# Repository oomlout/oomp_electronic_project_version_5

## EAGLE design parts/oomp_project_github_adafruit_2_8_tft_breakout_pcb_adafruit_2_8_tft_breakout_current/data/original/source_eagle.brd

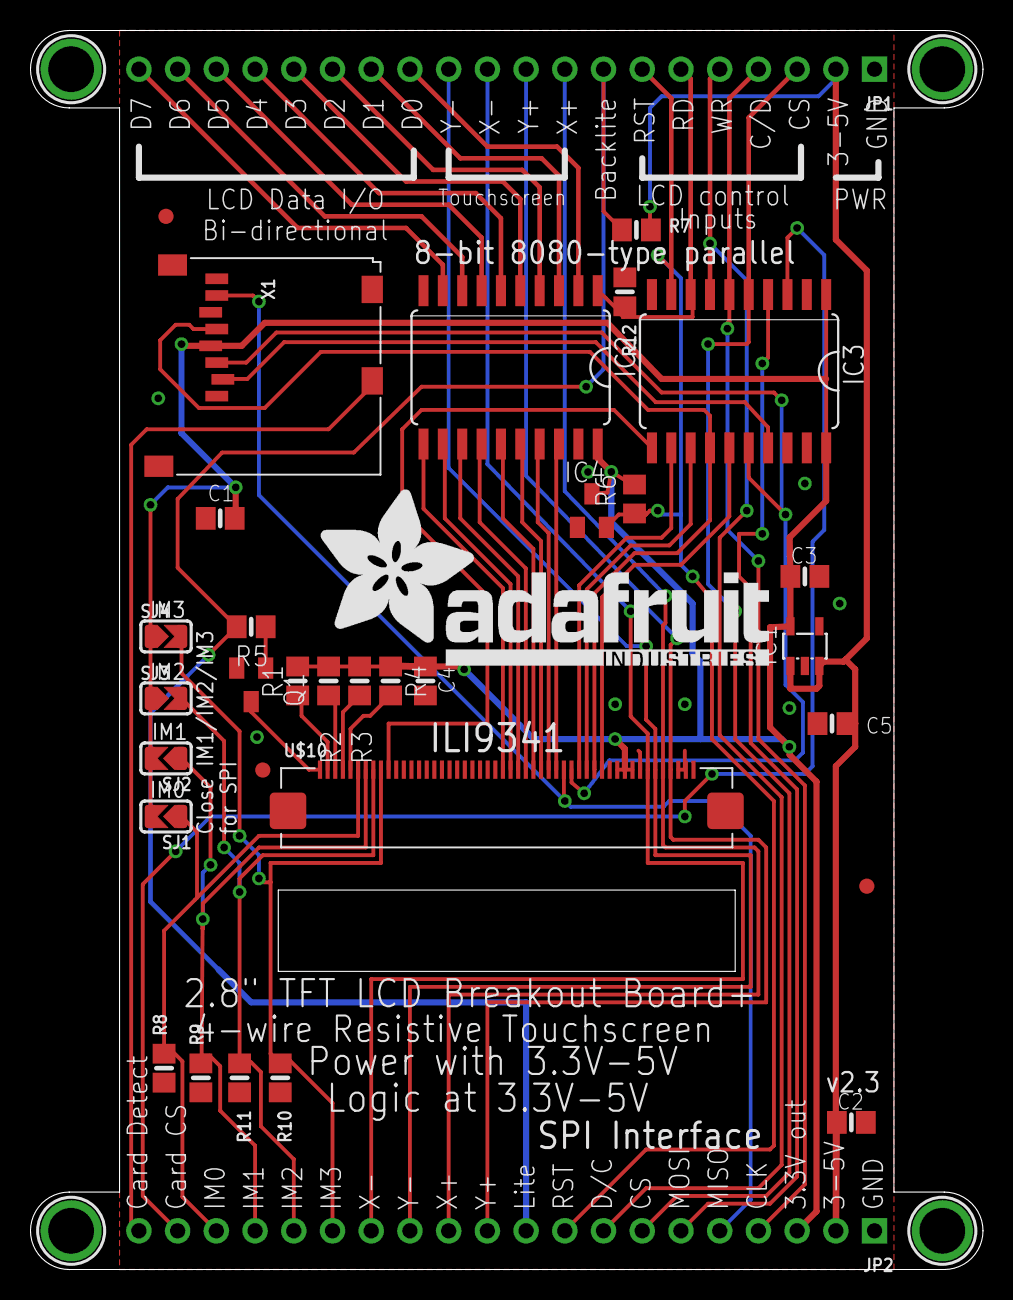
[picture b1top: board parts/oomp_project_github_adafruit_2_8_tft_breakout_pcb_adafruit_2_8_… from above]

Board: 2 copper layers, 62.5 x 81.3 mm, 38 parts (1 on the bottom side), 50 nets.

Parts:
C1, C4: 0.1uF; 0805-NO
C2, C3, C5: 10uF; 0805-NO
IC1: MIC5225-3.3; SOT23-5L
IC2, IC3: 74LVC245; SO20W
IC4: APX803-SAG; SOT23
JP1, JP2: 1X20_ROUND
Q1: MMBT2222; SOT23-BEC
R1, R2, R3, R4: 10; 0805-NO
R5, R7: 1K; 0805-NO
R6: 10K; R0805
R8, R9, R10, R11, R12: 10K; 0805-NO
SJ1, SJ2, SJ3, SJ4: SOLDERJUMPER_ARROW_NOPASTE
U$7, U$15, U$16, U$17: MOUNTINGHOLE3.0THIN; MOUNTINGHOLE_3.0_PLATEDTHIN
U$9, U$11, U$23: FIDUCIAL; FIDUCIAL_1MM
U$10: DISP_LCD_1.28IN_240X320_50PIN; TFT_2.83IN_240X320_50PIN
U$19: ADAFRUIT_TEXT_30MM
X1: MICROSD

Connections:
+5V: C2.1, C5.1, IC1.1, IC1.3, JP1.2, JP2.2, R7.2
CARDDET: JP2.20, X1.CD2
GND: C1.2, C2.2, C3.2, C4.2, C5.2, IC1.2, IC2.10, IC2.19, IC3.10, IC3.19, IC4.1, JP1.1, JP2.1, Q1.E, R8.1, R9.1, R10.2, R11.2, R12.1, U$10.43, U$10.48, U$10.49, U$10.50, X1.6, X1.MT1, X1.MT2
IM0: JP2.18, R8.2, SJ1.1, U$10.6
IM1: JP2.17, R9.2, SJ2.1, U$10.7
IM2: JP2.16, R11.1, SJ3.2, U$10.8
IM3: JP2.15, R10.1, SJ4.2, U$10.9
LCD_CS: IC3.15, U$10.38
LCD_CS_5V: IC3.5, JP1.3, JP2.7
LCD_DATA0: IC2.18, U$10.32
LCD_DATA0_5V: IC2.2, JP1.13
LCD_DATA1: IC2.17, U$10.31
LCD_DATA1_5V: IC2.3, JP1.14
LCD_DATA2: IC2.16, U$10.30
LCD_DATA2_5V: IC2.4, JP1.15
LCD_DATA3: IC2.15, U$10.29
LCD_DATA3_5V: IC2.5, JP1.16
LCD_DATA4: IC2.14, U$10.28
LCD_DATA4_5V: IC2.6, JP1.17
LCD_DATA5: IC2.13, U$10.27
LCD_DATA5_5V: IC2.7, JP1.18
LCD_DATA6: IC2.12, U$10.26
LCD_DATA6_5V: IC2.8, JP1.19
LCD_DATA7: IC2.11, U$10.25
LCD_DATA7_5V: IC2.9, JP1.20
LCD_LITE: JP1.8, JP2.10, R5.1, R7.1
LCD_RD: IC3.12, U$10.35
LCD_RD_5V: IC2.1, IC3.8, JP1.6, R12.2
LCD_RS: IC3.14, U$10.37, X1.5
LCD_RST: IC3.11, U$10.10
LCD_RST_5V: IC3.9, IC4.2, JP1.7, JP2.9, R6.1
LCD_RS_5V: IC3.6, JP1.4, JP2.4
LCD_WR: IC3.13, U$10.36
LCD_WR_5V: IC3.7, JP1.5, JP2.8
LCD_X+: JP1.9, JP2.12, U$10.46
LCD_X-: JP1.11, JP2.14, U$10.44
LCD_Y+: JP1.10, JP2.11, U$10.47
LCD_Y-: JP1.12, JP2.13, U$10.45
unnamed: R4.2, U$10.5
unnamed: R1.2, U$10.2
unnamed: R2.2, U$10.3
unnamed: R3.2, U$10.4
unnamed: Q1.C, U$10.1
unnamed: Q1.B, R5.2
SDI_3V: IC3.16, U$10.34, X1.3
SDI_5V: IC3.4, JP2.6
SDO: JP2.5, U$10.33, X1.7
SD_CS_3V: IC3.17, X1.2
SD_CS_5V: IC3.3, JP2.19
VCC: C1.1, C3.1, C4.1, IC1.5, IC2.20, IC3.1, IC3.20, IC4.3, JP2.3, R1.1, R2.1, R3.1, R4.1, R6.2, SJ1.2, SJ2.2, SJ3.1, SJ4.1, U$10.40, U$10.41, U$10.42, X1.4

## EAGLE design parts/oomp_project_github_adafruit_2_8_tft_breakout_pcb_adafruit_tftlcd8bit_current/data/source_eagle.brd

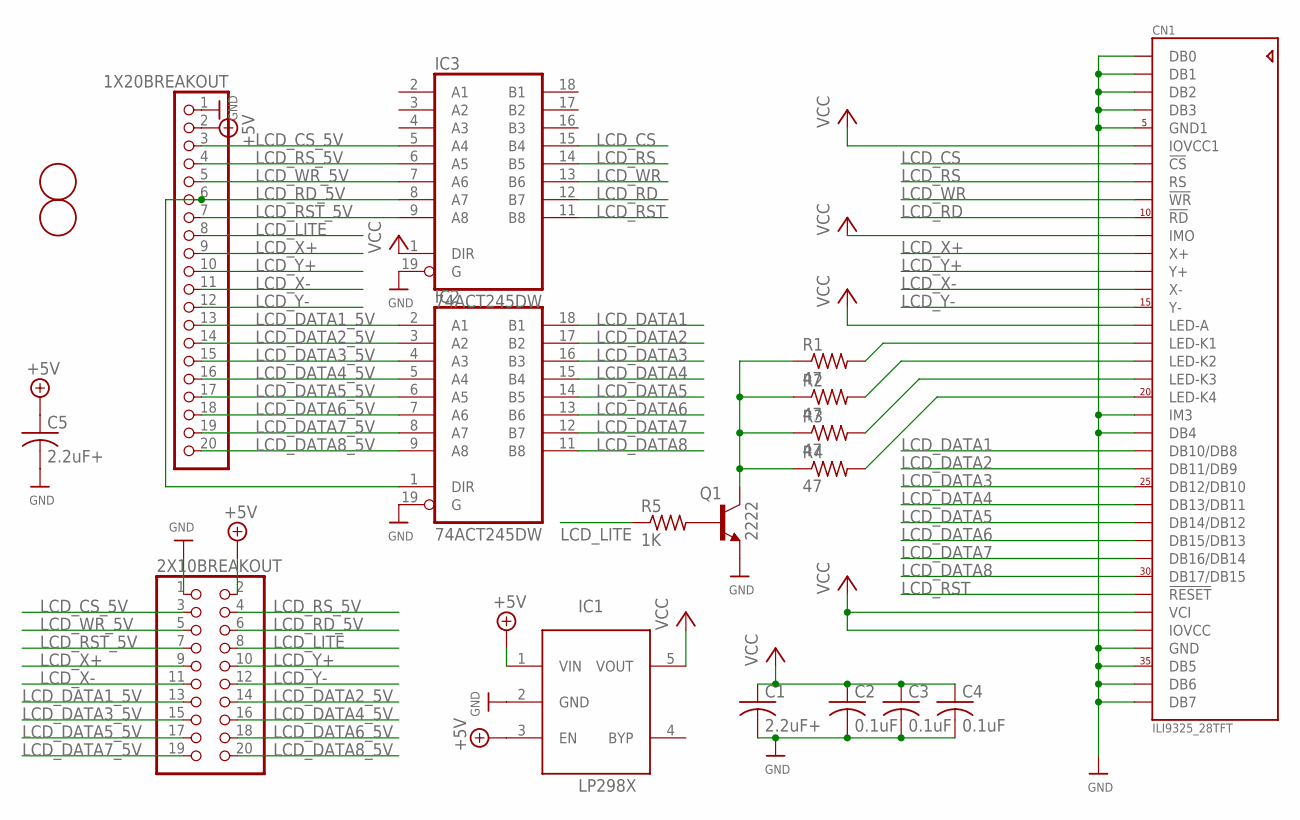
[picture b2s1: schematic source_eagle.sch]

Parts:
1X20BREAKOUT: PINHD-1X20; 1X20
2X10BREAKOUT: PINHD-2X10; 2X10
C1, C5: 2.2uF+; C0805K
C2, C3, C4: 0.1uF; C0805K
CN1: ILI9325_28TFT; ILI9325_28INCH_TS
IC1: LP298XS; SOT23-5L
IC2, IC3: 74ACT245DW; SO20W
Q1: 2222; SOT23-BEC
R1, R2, R3, R4: 47; R0805
R5: 1K; R0805
U$9, U$11: FIDUCIAL; FIDUCIAL_1MM

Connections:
+5V: 1X20BREAKOUT.2, 2X10BREAKOUT.2, C5.1, IC1.1 (VIN), IC1.3 (EN)
GND: 1X20BREAKOUT.1, 2X10BREAKOUT.1, C1.2, C2.2, C3.2, C4.2, C5.2, CN1.1 (DB0), CN1.2 (DB1), CN1.3 (DB2), CN1.4 (DB3), CN1.5 (GND1), CN1.21 (IM3), CN1.22 (DB4), CN1.34 (GND), CN1.35 (DB5), CN1.36 (DB6), CN1.37 (DB7), IC1.2 (GND), IC2.10 (GND), IC2.19 (G), IC3.10 (GND), IC3.19 (G), Q1.E
LCD_CS: CN1.7 (!CS), IC3.15 (B4)
LCD_CS_5V: 1X20BREAKOUT.3, 2X10BREAKOUT.3, IC3.5 (A4)
LCD_DATA1: CN1.23 (DB10/DB8), IC2.18 (B1)
LCD_DATA1_5V: 1X20BREAKOUT.13, 2X10BREAKOUT.13, IC2.2 (A1)
LCD_DATA2: CN1.24 (DB11/DB9), IC2.17 (B2)
LCD_DATA2_5V: 1X20BREAKOUT.14, 2X10BREAKOUT.14, IC2.3 (A2)
LCD_DATA3: CN1.25 (DB12/DB10), IC2.16 (B3)
LCD_DATA3_5V: 1X20BREAKOUT.15, 2X10BREAKOUT.15, IC2.4 (A3)
LCD_DATA4: CN1.26 (DB13/DB11), IC2.15 (B4)
LCD_DATA4_5V: 1X20BREAKOUT.16, 2X10BREAKOUT.16, IC2.5 (A4)
LCD_DATA5: CN1.27 (DB14/DB12), IC2.14 (B5)
LCD_DATA5_5V: 1X20BREAKOUT.17, 2X10BREAKOUT.17, IC2.6 (A5)
LCD_DATA6: CN1.28 (DB15/DB13), IC2.13 (B6)
LCD_DATA6_5V: 1X20BREAKOUT.18, 2X10BREAKOUT.18, IC2.7 (A6)
LCD_DATA7: CN1.29 (DB16/DB14), IC2.12 (B7)
LCD_DATA7_5V: 1X20BREAKOUT.19, 2X10BREAKOUT.19, IC2.8 (A7)
LCD_DATA8: CN1.30 (DB17/DB15), IC2.11 (B8)
LCD_DATA8_5V: 1X20BREAKOUT.20, 2X10BREAKOUT.20, IC2.9 (A8)
LCD_LITE: 1X20BREAKOUT.8, 2X10BREAKOUT.8, R5.1
LCD_RD: CN1.10 (!RD), IC3.12 (B7)
LCD_RD_5V: 1X20BREAKOUT.6, 2X10BREAKOUT.6, IC2.1 (DIR), IC3.8 (A7)
LCD_RS: CN1.8 (RS), IC3.14 (B5)
LCD_RST: CN1.31 (!RESET), IC3.11 (B8)
LCD_RST_5V: 1X20BREAKOUT.7, 2X10BREAKOUT.7, IC3.9 (A8)
LCD_RS_5V: 1X20BREAKOUT.4, 2X10BREAKOUT.4, IC3.6 (A5)
LCD_WR: CN1.9 (!WR), IC3.13 (B6)
LCD_WR_5V: 1X20BREAKOUT.5, 2X10BREAKOUT.5, IC3.7 (A6)
LCD_X+: 1X20BREAKOUT.9, 2X10BREAKOUT.9, CN1.12 (X+)
LCD_X-: 1X20BREAKOUT.11, 2X10BREAKOUT.11, CN1.14 (X-)
LCD_Y+: 1X20BREAKOUT.10, 2X10BREAKOUT.10, CN1.13 (Y+)
LCD_Y-: 1X20BREAKOUT.12, 2X10BREAKOUT.12, CN1.15 (Y-)
unnamed: CN1.20 (LED-K4), R4.2
unnamed: CN1.17 (LED-K1), R1.2
unnamed: CN1.18 (LED-K2), R2.2
unnamed: CN1.19 (LED-K3), R3.2
unnamed: Q1.C, R1.1, R2.1, R3.1, R4.1
unnamed: Q1.B, R5.2
VCC: C1.1, C2.1, C3.1, C4.1, CN1.6 (IOVCC1), CN1.11 (IMO), CN1.16 (LED-A), CN1.32 (VCI), CN1.33 (IOVCC), IC1.5 (VOUT), IC2.20 (VCC), IC3.1 (DIR), IC3.20 (VCC)

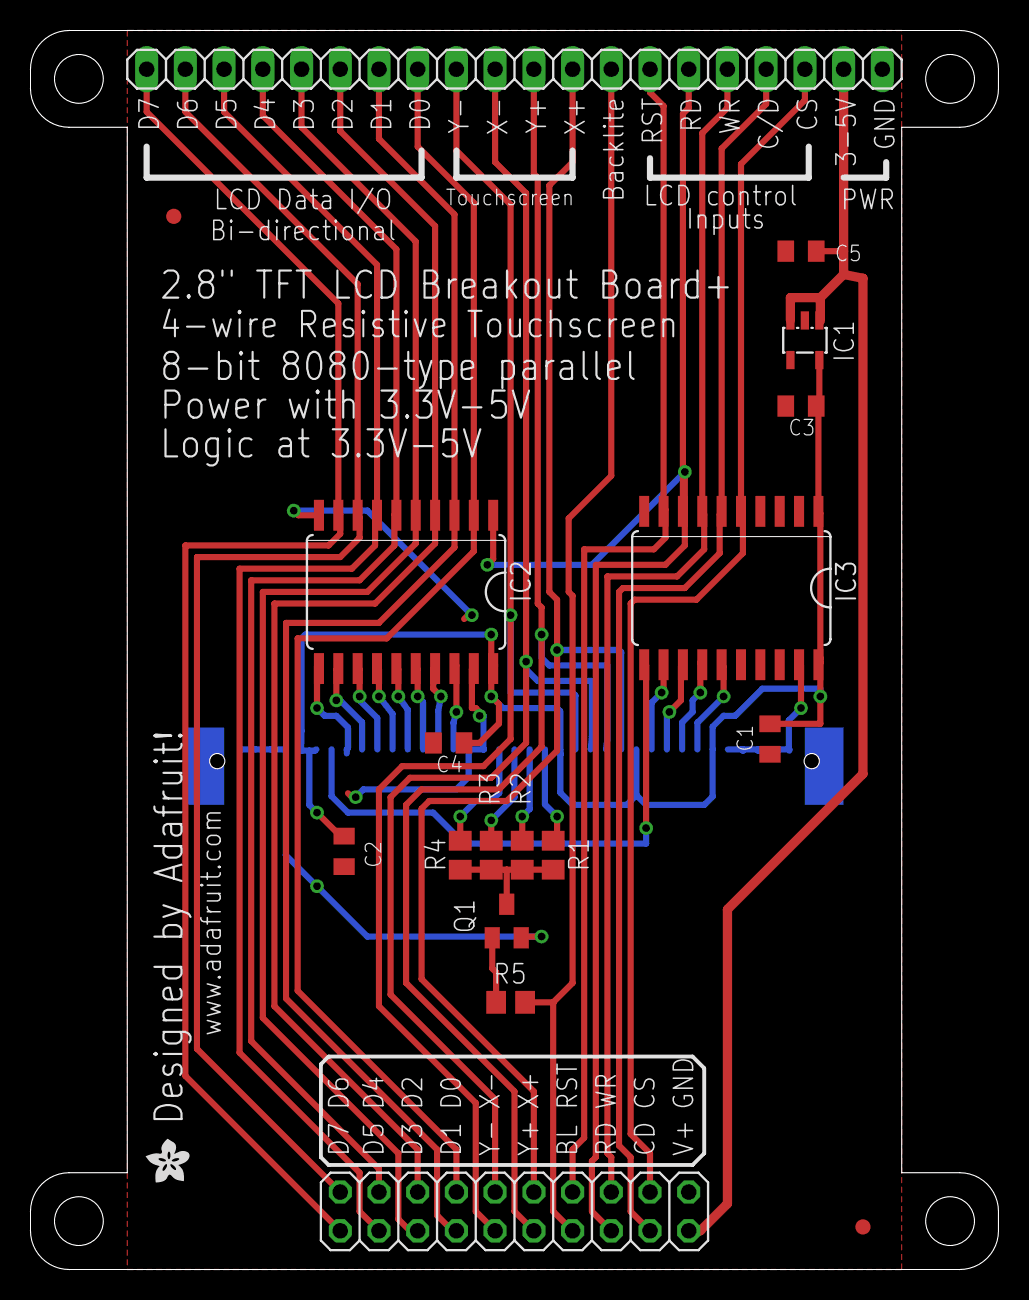
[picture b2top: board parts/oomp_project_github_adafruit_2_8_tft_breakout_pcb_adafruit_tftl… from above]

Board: 2 copper layers, 63.5 x 81.3 mm, 20 parts (1 on the bottom side), 40 nets.

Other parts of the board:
U$3: ADAFRUIT200MIL

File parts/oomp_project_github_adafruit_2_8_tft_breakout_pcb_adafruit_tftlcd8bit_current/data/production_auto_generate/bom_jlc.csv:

Comment,Designator,Footprint,LCSC Part #
,UNK1X20BREAKOUT0,Adafruit_tftlcd8bit-import-fps:1X20,C50981
,UNK2X10BREAKOUT0,Adafruit_tftlcd8bit-import-fps:2X10,
,U$3,Adafruit_tftlcd8bit-import-fps:ADAFRUIT200MIL,
0.1uF,"C2,C3,C4",Adafruit_tftlcd8bit-import-fps:C0805K,
1K,R5,Adafruit_tftlcd8bit-import-fps:R0805,C17513
2.2uF+,"C1,C5",Adafruit_tftlcd8bit-import-fps:C0805K,
2222,Q1,Adafruit_tftlcd8bit-import-fps:SOT23-BEC,
47,"R1,R2,R3,R4",Adafruit_tftlcd8bit-import-fps:R0805,C2907268
74ACT245DW,"IC2,IC3",Adafruit_tftlcd8bit-import-fps:SO20W,
FIDUCIAL,"U$9,U$11",Adafruit_tftlcd8bit-import-fps:FIDUCIAL_1MM,
ILI9325_28TFT,CN1,Adafruit_tftlcd8bit-import-fps:ILI9325_28INCH_TS,
LP298XS,IC1,Adafruit_tftlcd8bit-import-fps:SOT23-5L,

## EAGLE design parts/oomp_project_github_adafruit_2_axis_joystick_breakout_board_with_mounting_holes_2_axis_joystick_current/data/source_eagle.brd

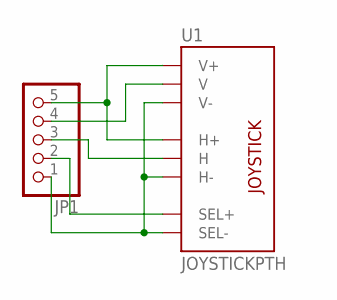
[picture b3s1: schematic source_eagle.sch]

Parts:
JP1: PINHD-1X5; 1X05
U1: JOYSTICKPTH; JOYSTICK

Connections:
unnamed: JP1.5, U1.H1 (H+), U1.V1 (V+)
unnamed: JP1.1, U1.B2A (SEL-), U1.H3 (H-), U1.V3 (V-)
unnamed: JP1.4, U1.V2 (V)
unnamed: JP1.3, U1.H2 (H)
unnamed: JP1.2, U1.B1A (SEL+)

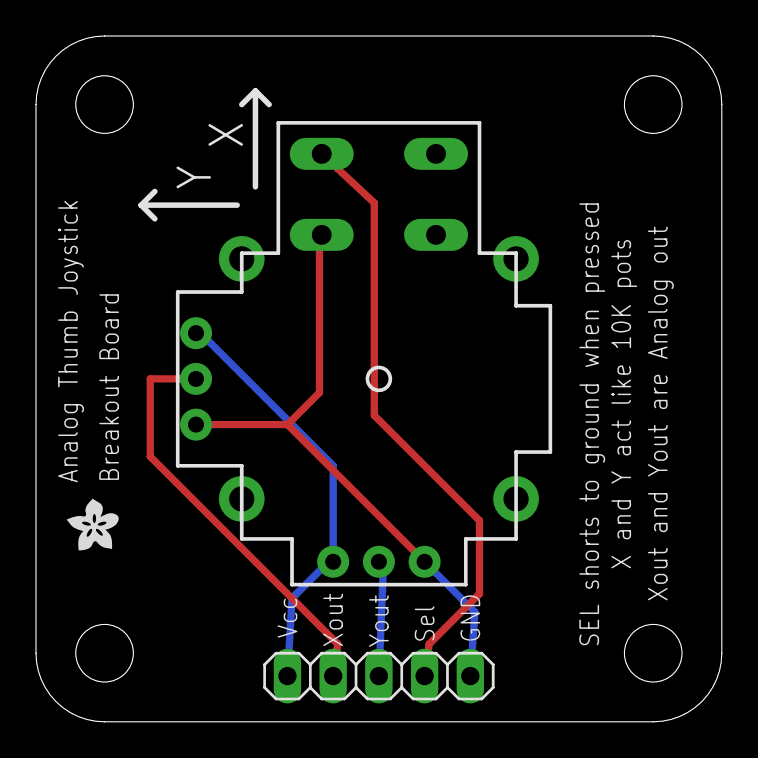
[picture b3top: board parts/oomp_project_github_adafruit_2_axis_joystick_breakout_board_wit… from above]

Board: 2 copper layers, 38.1 x 38.1 mm, 3 parts (0 on the bottom side), 5 nets.

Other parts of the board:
U$1: ADAFRUIT200MIL

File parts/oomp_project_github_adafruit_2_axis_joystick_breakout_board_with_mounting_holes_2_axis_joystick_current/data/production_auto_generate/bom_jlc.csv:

Comment,Designator,Footprint,LCSC Part #
,JP1,joystick-import-fps:1X05,C42431835
,U$1,joystick-import-fps:ADAFRUIT200MIL,
JOYSTICKPTH,U1,joystick-import-fps:JOYSTICK,

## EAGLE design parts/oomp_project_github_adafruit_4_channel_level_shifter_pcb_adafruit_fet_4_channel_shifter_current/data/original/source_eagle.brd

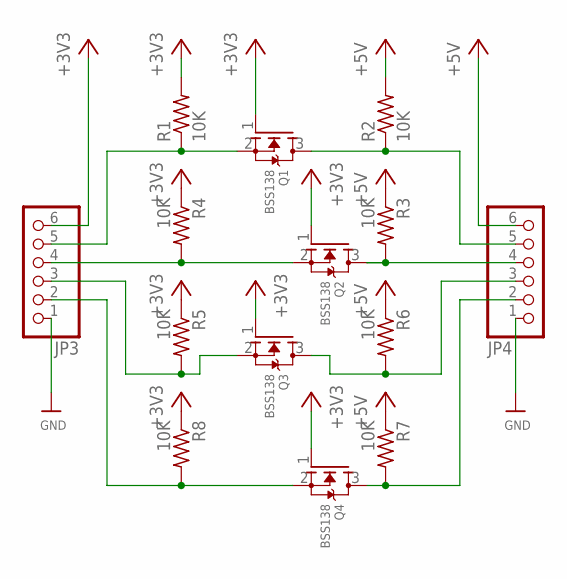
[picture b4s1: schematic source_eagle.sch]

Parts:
JP3, JP4: PINHD-1X6CB; 1X06-CLEANBIG
Q1, Q2, Q3, Q4: BSS138; SOT23
R1, R2, R3, R4, R5, R6, R7, R8: 10K; R0805

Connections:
+3V3: JP3.6, Q1.1 (G), Q2.1 (G), Q3.1 (G), Q4.1 (G), R1.2, R4.1, R5.1, R8.1
+5V: JP4.6, R2.2, R3.1, R6.1, R7.1
GND: JP3.1, JP4.1
unnamed: JP4.3, Q3.3 (D), R6.2
unnamed: JP4.5, Q1.3 (D), R2.1
unnamed: JP3.3, Q3.2 (S), R5.2
unnamed: JP3.2, Q4.2 (S), R8.2
unnamed: JP4.2, Q4.3 (D), R7.2
unnamed: JP3.4, Q2.2 (S), R4.2
unnamed: JP4.4, Q2.3 (D), R3.2
unnamed: JP3.5, Q1.2 (S), R1.1

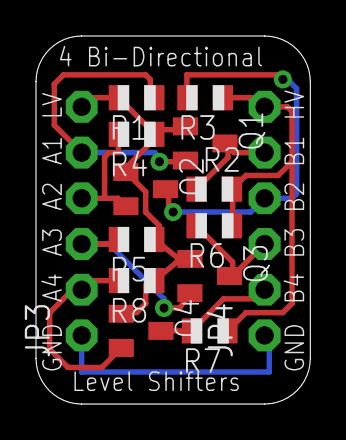
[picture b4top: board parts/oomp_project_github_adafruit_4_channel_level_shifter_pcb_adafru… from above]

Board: 2 copper layers, 15.2 x 20.4 mm, 15 parts (1 on the bottom side), 11 nets.

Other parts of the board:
U$1: ADAFRUIT_3.5MM

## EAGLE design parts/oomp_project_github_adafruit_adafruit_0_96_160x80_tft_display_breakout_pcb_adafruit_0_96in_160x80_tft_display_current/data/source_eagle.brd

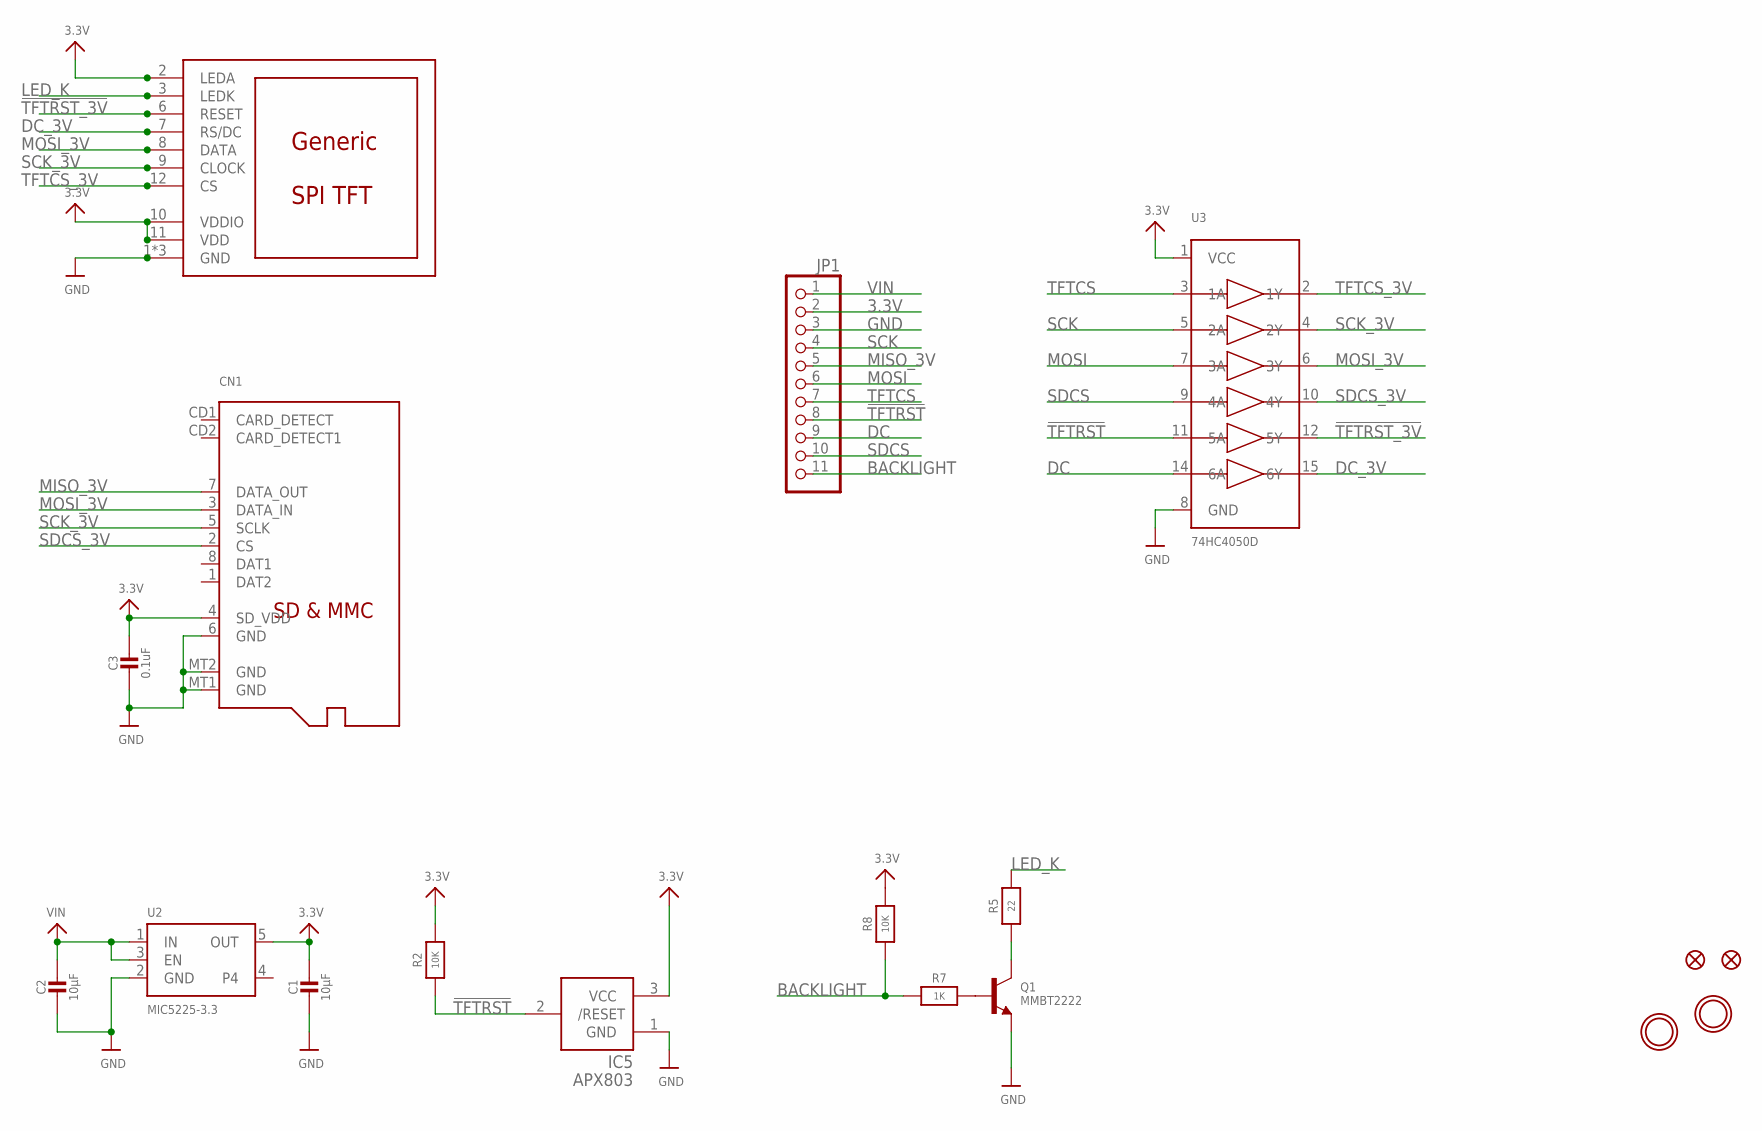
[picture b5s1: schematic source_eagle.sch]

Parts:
C1, C2: 10µF; 0805-NO
C3: 0.1uF; 0805-NO
CN1: MICROSD
FID1, FID2: FIDUCIAL_1MM
IC5: APX803; SOT23
JP1: HEADER-1X11; 1X11_ROUND
Q1: MMBT2222; SOT23-WIDE
R2, R8: 10K; 0603-NO
R5: 22; 0603-NO
R7: 1K; 0603-NO
U2: MIC5225-3.3; SOT23-5
U3: 74HC4050D; SOIC16
U$2: DISP_LCD_0.9IN_160X80; TFT_0.96IN_160X80
U$9, U$10: MOUNTINGHOLE2.5; MOUNTINGHOLE_2.5_PLATED

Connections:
3.3V: C1.1, C3.1, CN1.4 (SD_VDD), IC5.3 (VCC), JP1.2, R2.2, R8.2, U2.5 (OUT), U3.1 (VCC), U$2.2 (LEDA), U$2.10 (VDDIO), U$2.11 (VDD)
!TFTRST: IC5.2 (/RESET), JP1.8, R2.1, U3.11 (5A)
!TFTRST_3V: U3.12 (5Y), U$2.6 (RESET)
BACKLIGHT: JP1.11, R7.1, R8.1
DC: JP1.9, U3.14 (6A)
DC_3V: U3.15 (6Y), U$2.7 (RS/DC)
GND: C1.2, C2.2, C3.2, CN1.6 (GND), CN1.MT1 (GND), CN1.MT2 (GND), IC5.1 (GND), JP1.3, Q1.2 (E), U2.2 (GND), U3.8 (GND), U$2.1 (GND), U$2.5 (GND), U$2.13 (GND)
LED_K: R5.2, U$2.3 (LEDK)
MISO_3V: CN1.7 (DATA_OUT), JP1.5
MOSI: JP1.6, U3.7 (3A)
MOSI_3V: CN1.3 (DATA_IN), U3.6 (3Y), U$2.8 (DATA)
unnamed: Q1.1 (B), R7.2
unnamed: Q1.3 (C), R5.1
SCK: JP1.4, U3.5 (2A)
SCK_3V: CN1.5 (SCLK), U3.4 (2Y), U$2.9 (CLOCK)
SDCS: JP1.10, U3.9 (4A)
SDCS_3V: CN1.2 (CS), U3.10 (4Y)
TFTCS: JP1.7, U3.3 (1A)
TFTCS_3V: U3.2 (1Y), U$2.12 (CS)
VIN: C2.1, JP1.1, U2.1 (IN), U2.3 (EN)

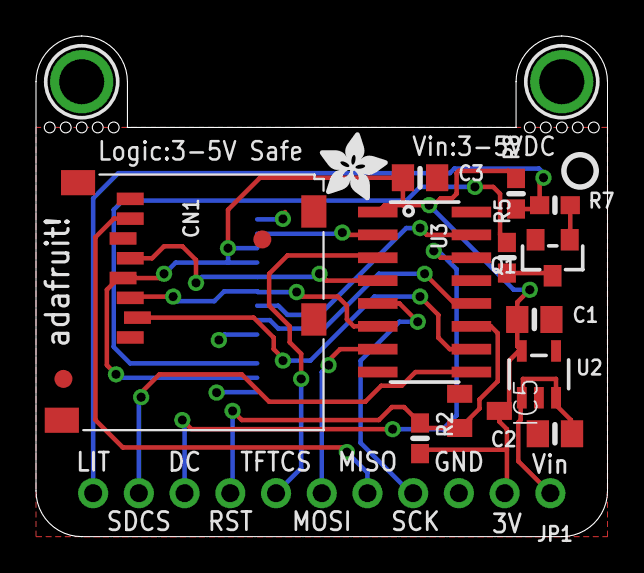
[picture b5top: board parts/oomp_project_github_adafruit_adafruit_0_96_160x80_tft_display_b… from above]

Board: 2 copper layers, 31.8 x 27.8 mm, 20 parts (1 on the bottom side), 20 nets.

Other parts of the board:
U$4: MICROSD; ADAFRUIT_3.5MM
U$6: PCBFEAT-REV-040

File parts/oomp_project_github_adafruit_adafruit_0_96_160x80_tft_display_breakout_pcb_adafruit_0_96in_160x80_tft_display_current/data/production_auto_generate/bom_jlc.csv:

Comment,Designator,Footprint,LCSC Part #
,JP1,Adafruit 0.96in 160x80 TFT Display-import-fps:1X11_ROUND,C2894934
,CN1,Adafruit 0.96in 160x80 TFT Display-import-fps:MICROSD,
,U$6,Adafruit 0.96in 160x80 TFT Display-import-fps:PCBFEAT-REV-040,
0.1uF,C3,Adafruit 0.96in 160x80 TFT Display-import-fps:0805-NO,
10K,"R2,R8",Adafruit 0.96in 160x80 TFT Display-import-fps:0603-NO,C98220
10µF,"C1,C2",Adafruit 0.96in 160x80 TFT Display-import-fps:0805-NO,
1K,R7,Adafruit 0.96in 160x80 TFT Display-import-fps:0603-NO,C2907002
22,R5,Adafruit 0.96in 160x80 TFT Display-import-fps:0603-NO,C23345
74HC4050D,U3,Adafruit 0.96in 160x80 TFT Display-import-fps:SOIC16,
APX803,IC5,Adafruit 0.96in 160x80 TFT Display-import-fps:SOT23,
DISP_LCD_0.9IN_160X80,U$2,Adafruit 0.96in 160x80 TFT Display-import-fps:TFT_0.96IN_160X80,
MIC5225-3.3,U2,Adafruit 0.96in 160x80 TFT Display-import-fps:SOT23-5,
MICROSD,U$4,Adafruit 0.96in 160x80 TFT Display-import-fps:ADAFRUIT_3.5MM,
MMBT2222,Q1,Adafruit 0.96in 160x80 TFT Display-import-fps:SOT23-WIDE,

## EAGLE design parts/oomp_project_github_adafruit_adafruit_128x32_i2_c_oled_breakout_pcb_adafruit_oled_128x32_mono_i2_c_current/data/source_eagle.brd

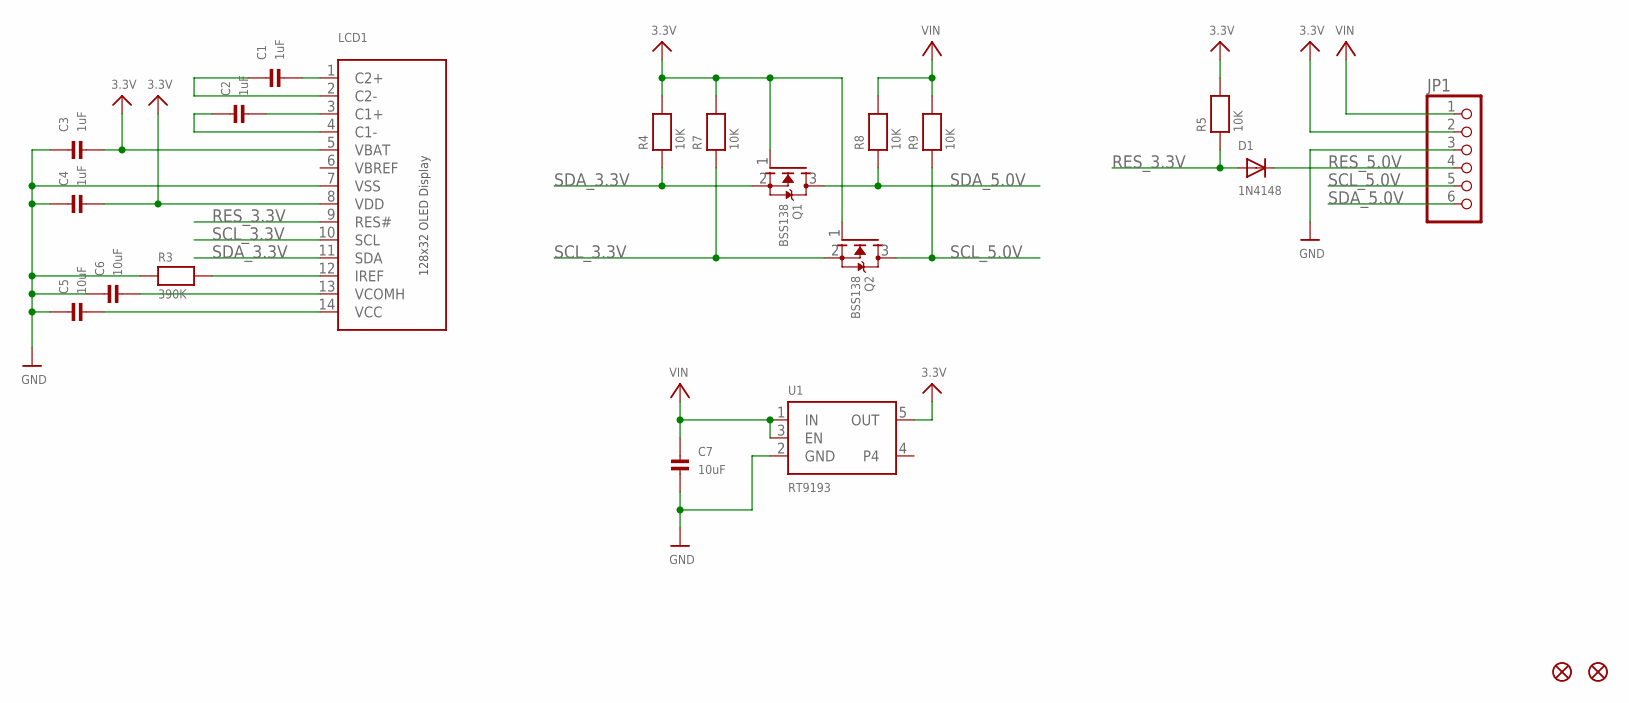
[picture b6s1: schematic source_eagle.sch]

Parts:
C1, C2, C3, C4: 1uF; 0805
C5, C6, C7: 10uF; 0805
D1: 1N4148; SOD-323F
FID1, FID2: FIDUCIAL""; FIDUCIAL_1MM
JP1: HEADER-1X670MIL; 1X06_ROUND_70
LCD1: DISP_OLED_UG-2832HSWEG02; UG-2832HSWEG02_WRAPUNDER
Q1, Q2: BSS138; SOT23-WIDE
R3: 390K; 0805
R4, R5, R7, R8, R9: 10K; 0805
U1: RT9193; SOT23-5

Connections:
3.3V: C3.2, C4.2, JP1.2, LCD1.5 (VBAT), LCD1.8 (VDD), Q1.1 (G), Q2.1 (G), R4.2, R5.2, R7.2, U1.5 (OUT)
GND: C3.1, C4.1, C5.1, C6.1, C7.2, JP1.3, LCD1.7 (VSS), R3.1, U1.2 (GND)
unnamed: C1.2, LCD1.1 (C2+)
unnamed: C1.1, LCD1.2 (C2-)
unnamed: C2.2, LCD1.3 (C1+)
unnamed: C2.1, LCD1.4 (C1-)
unnamed: C6.2, LCD1.13 (VCOMH)
unnamed: C5.2, LCD1.14 (VCC)
unnamed: LCD1.12 (IREF), R3.2
RES_3.3V: D1.A, LCD1.9 (RES#), R5.1
RES_5.0V: D1.C, JP1.4
SCL_3.3V: LCD1.10 (SCL), Q2.2 (S), R7.1
SCL_5.0V: JP1.5, Q2.3 (D), R9.1
SDA_3.3V: LCD1.11 (SDA), Q1.2 (S), R4.1
SDA_5.0V: JP1.6, Q1.3 (D), R8.1
VBREF: LCD1.6 (VBREF)
VIN: C7.1, JP1.1, R8.2, R9.2, U1.1 (IN), U1.3 (EN)

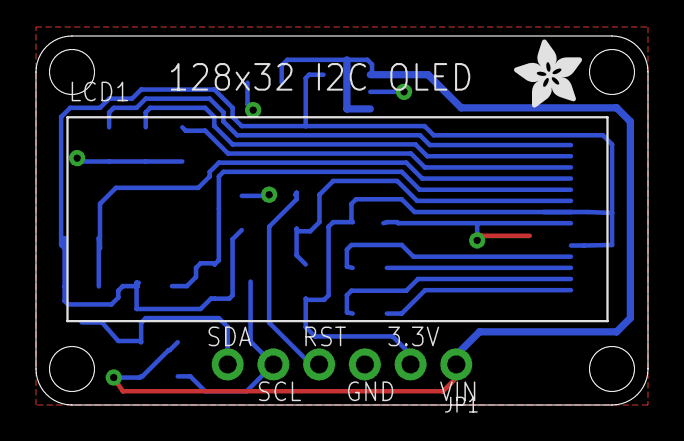
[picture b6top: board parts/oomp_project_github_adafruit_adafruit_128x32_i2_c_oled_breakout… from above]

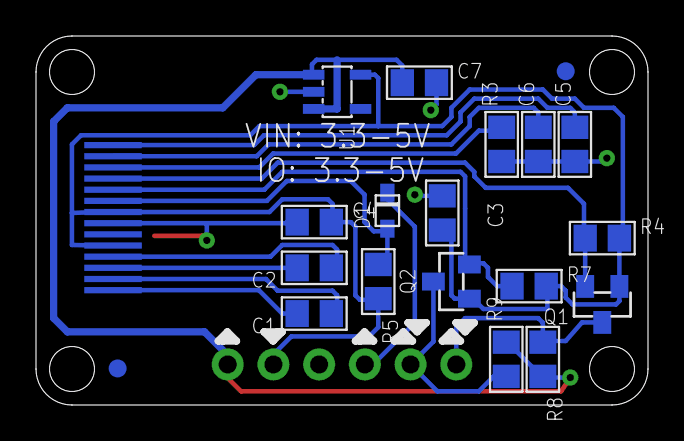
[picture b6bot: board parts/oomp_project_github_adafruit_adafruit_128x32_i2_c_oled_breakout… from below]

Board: 2 copper layers, 34.0 x 20.5 mm, 22 parts (19 on the bottom side), 16 nets.

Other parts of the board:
U$16: ADAFRUIT_3.5MM

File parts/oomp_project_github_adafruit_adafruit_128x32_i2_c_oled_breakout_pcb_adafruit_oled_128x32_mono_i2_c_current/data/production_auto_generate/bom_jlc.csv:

Comment,Designator,Footprint,LCSC Part #
,JP1,Adafruit OLED 128x32 Mono I2C-import-fps:1X06_ROUND_70,C37208
,U$16,Adafruit OLED 128x32 Mono I2C-import-fps:ADAFRUIT_3.5MM,
,LCD1,Adafruit OLED 128x32 Mono I2C-import-fps:UG-2832HSWEG02_WRAPUNDER,
10K,"R4,R5,R7,R8,R9",Adafruit OLED 128x32 Mono I2C-import-fps:0805,C17414
10uF,"C5,C6,C7",Adafruit OLED 128x32 Mono I2C-import-fps:0805,
1N4148,D1,Adafruit OLED 128x32 Mono I2C-import-fps:SOD-323F,
1uF,"C1,C2,C3,C4",Adafruit OLED 128x32 Mono I2C-import-fps:0805,
390K,R3,Adafruit OLED 128x32 Mono I2C-import-fps:0805,C17656
BSS138,"Q1,Q2",Adafruit OLED 128x32 Mono I2C-import-fps:SOT23-WIDE,C52895
RT9193,U1,Adafruit OLED 128x32 Mono I2C-import-fps:SOT23-5,

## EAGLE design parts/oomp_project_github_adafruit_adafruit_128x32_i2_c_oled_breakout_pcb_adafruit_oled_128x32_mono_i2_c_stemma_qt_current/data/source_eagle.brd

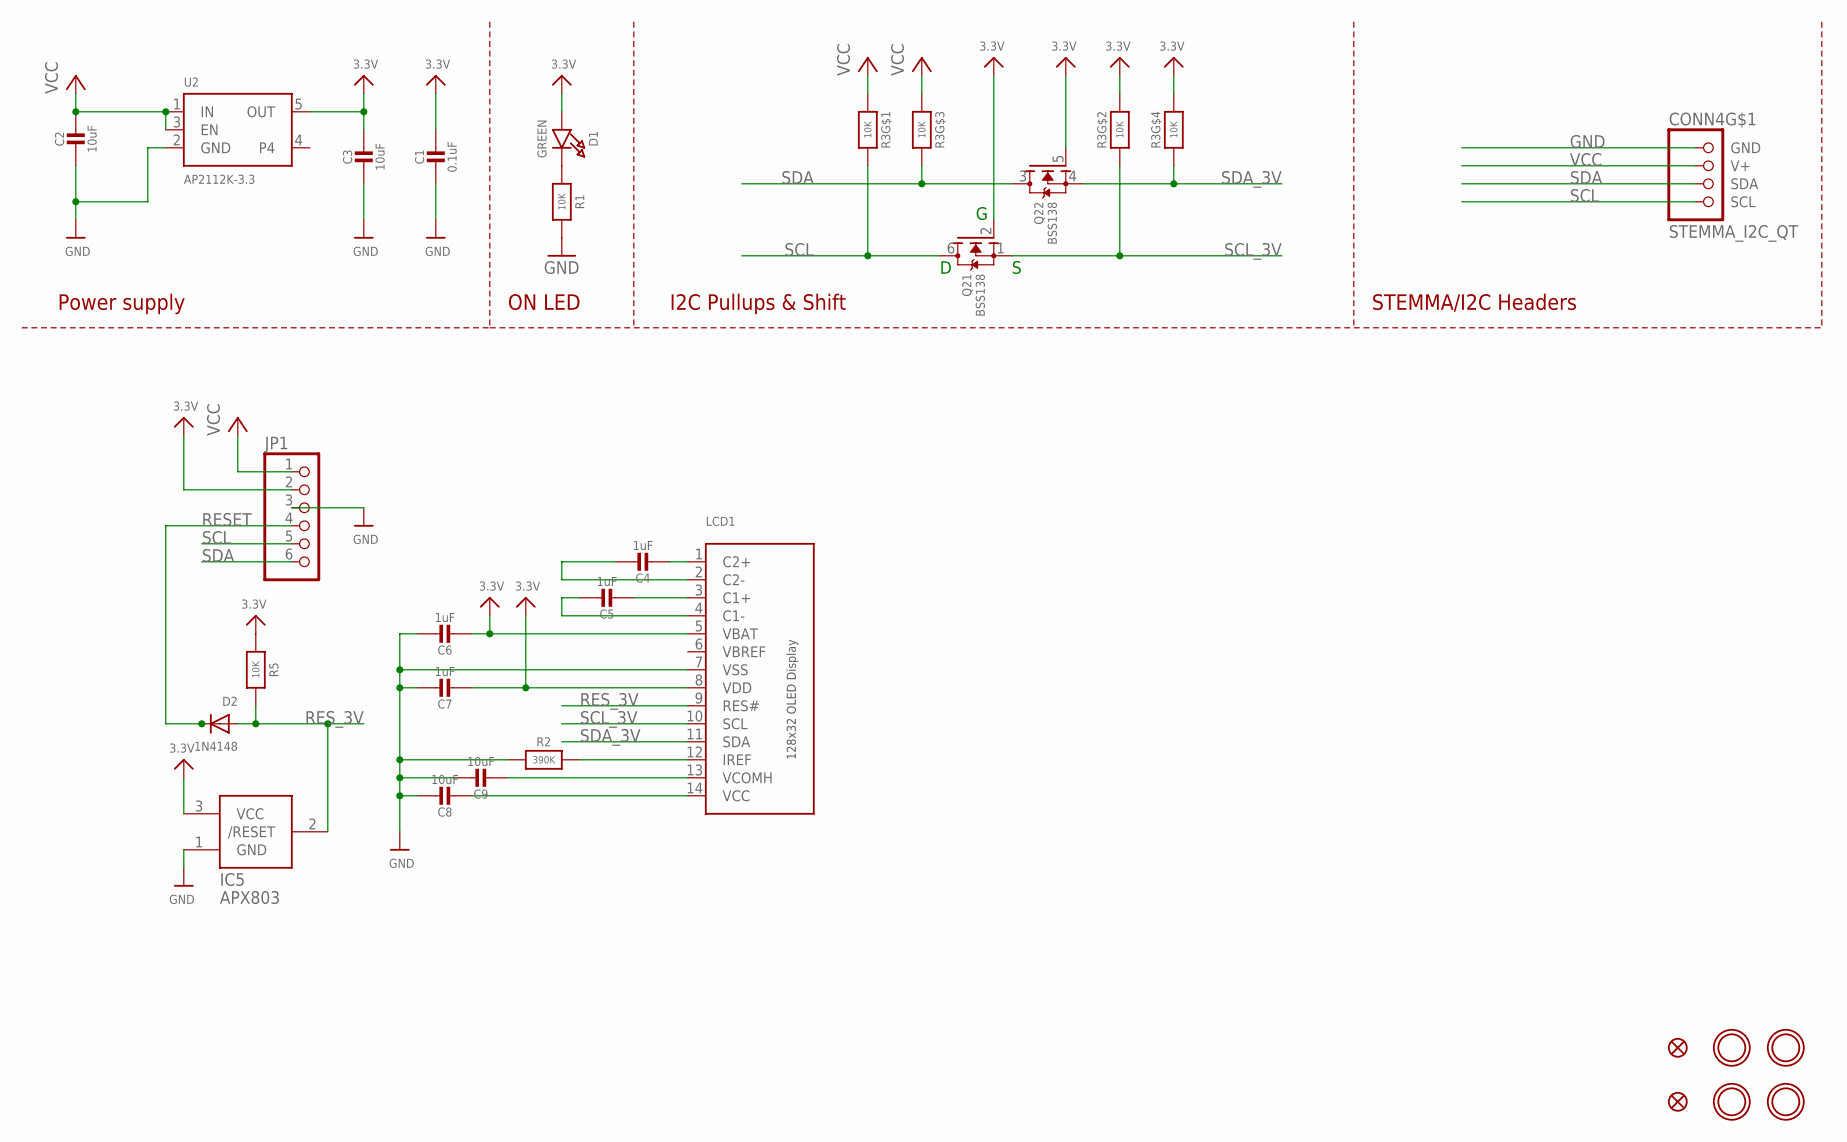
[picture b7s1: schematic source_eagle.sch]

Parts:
C1: 0.1uF; 0603-NO
C2, C3, C8, C9: 10uF; 0805-NO
C4, C5, C6, C7: 1uF; 0805-NO
CONN4: STEMMA_I2C_QT; JST_SH4
D1: GREEN; CHIPLED_0603_NOOUTLINE
D2: 1N4148; SOD-323F
FID3, FID4: FIDUCIAL_1MM
IC5: APX803; SOT23
JP1: HEADER-1X670MIL; 1X06_ROUND_70
LCD1: DISP_OLED_UG-2832HSWEG02; UG-2832HSWEG02_WRAPUNDER
Q2: BSS138; SOT363
R1, R5: 10K; 0603-NO
R2: 390K; 0603-NO
R3: 10K; RESPACK_4X0603
U2: AP2112K-3.3; SOT23-5
U$1, U$17, U$19, U$21: MOUNTINGHOLE2.5; MOUNTINGHOLE_2.5_PLATED

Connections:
3.3V: C1.1, C3.1, C6.2, C7.2, D1.A, IC5.3 (VCC), JP1.2, LCD1.5 (VBAT), LCD1.8 (VDD), Q2.2 (G), Q2.5 (G), R3.2 (1), R3.4 (1), R5.2, U2.5 (OUT)
GND: C1.2, C2.2, C3.2, C6.1, C7.1, C8.1, C9.1, CONN4.1 (GND), IC5.1 (GND), JP1.3, LCD1.7 (VSS), R1.2, R2.1, U2.2 (GND)
unnamed: C4.2, LCD1.1 (C2+)
unnamed: D1.C, R1.1
unnamed: C4.1, LCD1.2 (C2-)
unnamed: C5.2, LCD1.3 (C1+)
unnamed: C5.1, LCD1.4 (C1-)
unnamed: C9.2, LCD1.13 (VCOMH)
unnamed: LCD1.12 (IREF), R2.2
unnamed: C8.2, LCD1.14 (VCC)
RESET: D2.C, JP1.4
RES_3V: D2.A, IC5.2 (/RESET), LCD1.9 (RES#), R5.1
SCL: CONN4.4 (SCL), JP1.5, Q2.6 (D), R3.8 (2)
SCL_3V: LCD1.10 (SCL), Q2.1 (S), R3.7 (2)
SDA: CONN4.3 (SDA), JP1.6, Q2.3 (D), R3.6 (2)
SDA_3V: LCD1.11 (SDA), Q2.4 (S), R3.5 (2)
VBREF: LCD1.6 (VBREF)
VCC: C2.1, CONN4.2 (V+), JP1.1, R3.1, R3.3 (1), U2.1 (IN), U2.3 (EN)

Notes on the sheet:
I2C Pullups & Shift
STEMMA/I2C Headers
ON LED
Power supply

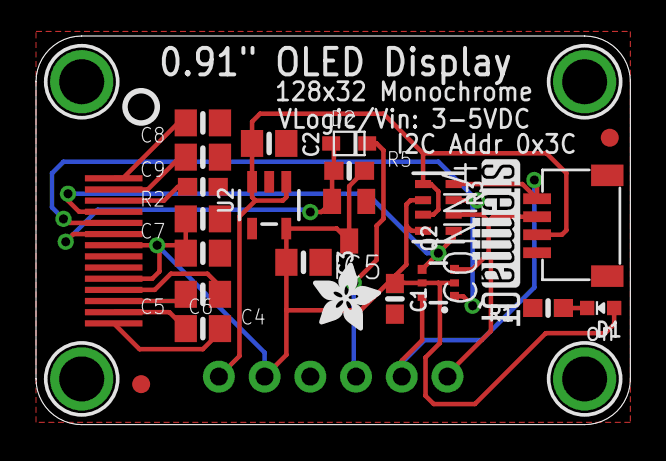
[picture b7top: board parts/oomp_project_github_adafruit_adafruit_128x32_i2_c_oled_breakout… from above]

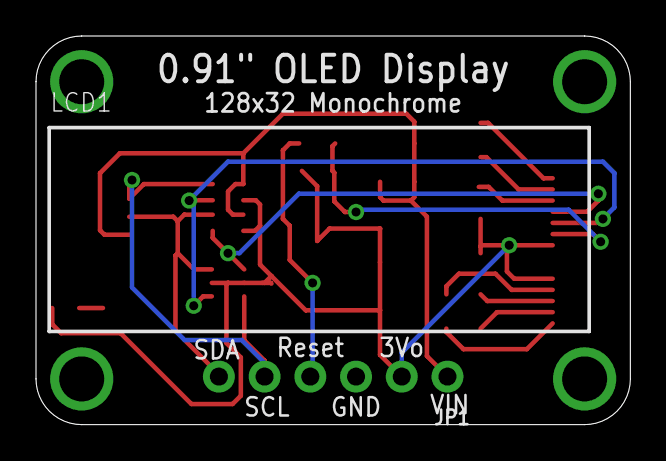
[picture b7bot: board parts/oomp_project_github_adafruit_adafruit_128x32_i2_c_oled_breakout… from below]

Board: 2 copper layers, 33.0 x 21.6 mm, 30 parts (2 on the bottom side), 17 nets.

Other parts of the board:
U$22: ADAFRUIT_3.5MM
U$25: PCBFEAT-REV-040
U$31: STEMMAQT

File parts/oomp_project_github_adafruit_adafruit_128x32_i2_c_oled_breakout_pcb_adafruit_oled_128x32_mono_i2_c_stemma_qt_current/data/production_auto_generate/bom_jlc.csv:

Comment,Designator,Footprint,LCSC Part #
,JP1,Adafruit OLED 128x32 Mono I2C STEMMA QT rev B-import-fps:1X06_ROUND_70,C37208
,U$22,Adafruit OLED 128x32 Mono I2C STEMMA QT rev B-import-fps:ADAFRUIT_3.5MM,
,U$25,Adafruit OLED 128x32 Mono I2C STEMMA QT rev B-import-fps:PCBFEAT-REV-040,
,U$31,Adafruit OLED 128x32 Mono I2C STEMMA QT rev B-import-fps:STEMMAQT,
,LCD1,Adafruit OLED 128x32 Mono I2C STEMMA QT rev B-import-fps:UG-2832HSWEG02_WRAPUNDER,
0.1uF,C1,Adafruit OLED 128x32 Mono I2C STEMMA QT rev B-import-fps:0603-NO,C14663
10K,"R1,R5",Adafruit OLED 128x32 Mono I2C STEMMA QT rev B-import-fps:0603-NO,C98220
10K,R3,Adafruit OLED 128x32 Mono I2C STEMMA QT rev B-import-fps:RESPACK_4X0603,C98220
10uF,"C2,C3,C8,C9",Adafruit OLED 128x32 Mono I2C STEMMA QT rev B-import-fps:0805-NO,
1N4148,D2,Adafruit OLED 128x32 Mono I2C STEMMA QT rev B-import-fps:SOD-323F,
1uF,"C4,C5,C6,C7",Adafruit OLED 128x32 Mono I2C STEMMA QT rev B-import-fps:0805-NO,
390K,R2,Adafruit OLED 128x32 Mono I2C STEMMA QT rev B-import-fps:0603-NO,C2907030
AP2112K-3.3,U2,Adafruit OLED 128x32 Mono I2C STEMMA QT rev B-import-fps:SOT23-5,
APX803,IC5,Adafruit OLED 128x32 Mono I2C STEMMA QT rev B-import-fps:SOT23,
BSS138,Q2,Adafruit OLED 128x32 Mono I2C STEMMA QT rev B-import-fps:SOT363,
GREEN,D1,Adafruit OLED 128x32 Mono I2C STEMMA QT rev B-import-fps:CHIPLED_0603_NOOUTLINE,
STEMMA_I2C_QT,CONN4,Adafruit OLED 128x32 Mono I2C STEMMA QT rev B-import-fps:JST_SH4,C160404

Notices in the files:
parts and their libraries:
microbuilder: This work is placed in the public domain, and may be freely used for commercial and non-commercial work with the following conditions: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
